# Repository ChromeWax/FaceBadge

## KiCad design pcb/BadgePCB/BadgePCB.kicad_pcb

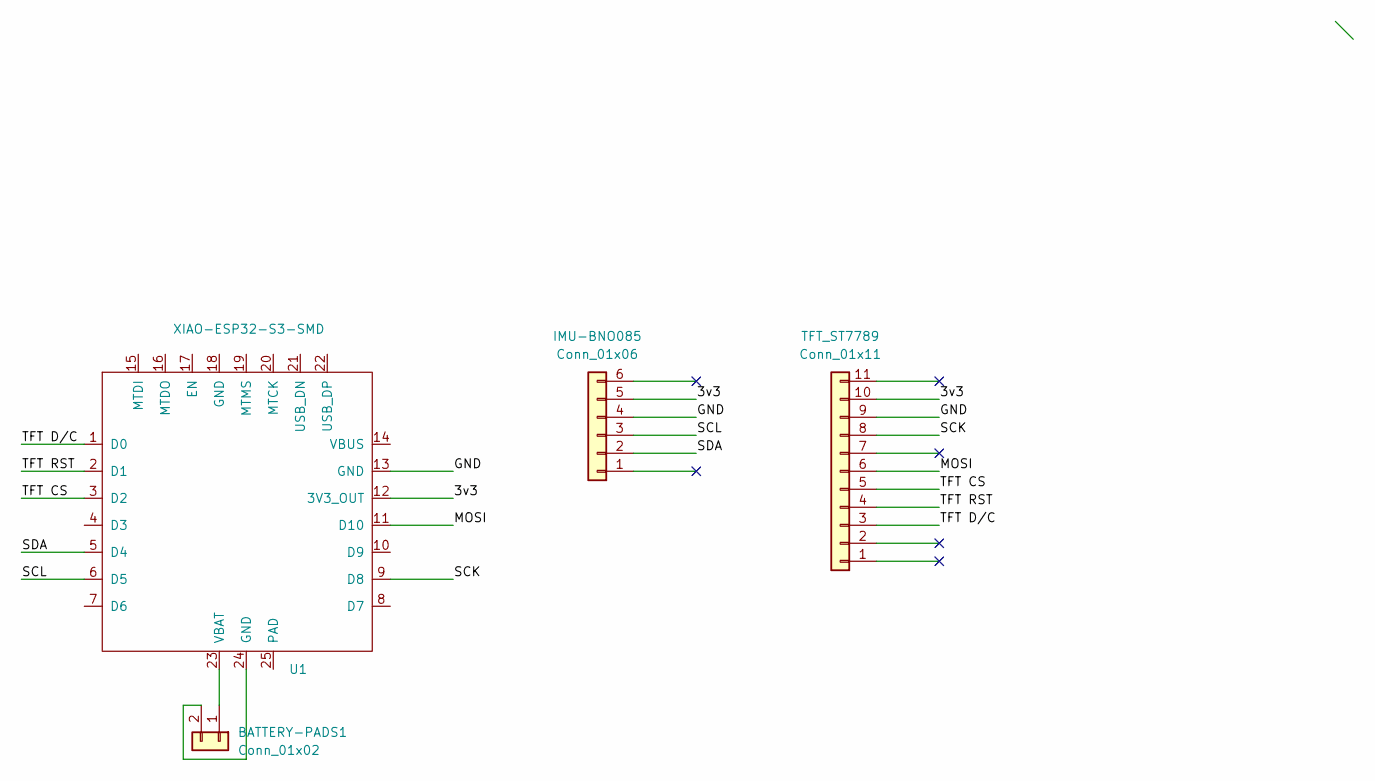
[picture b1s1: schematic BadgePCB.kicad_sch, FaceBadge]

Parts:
BATTERY-PADS1: Conn_01x02; Molex_PicoBlade_53261-0271_1x02-1MP_P1.25mm_Horizontal
IMU-BNO085: Conn_01x06; PinHeader_1x06_P2.54mm_Vertical
TFT_ST7789: Conn_01x11; PinHeader_1x11_P2.54mm_Vertical
U1: XIAO-ESP32-S3-SMD

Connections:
/3v3: IMU-BNO085.5, TFT_ST7789.10, U1.12 (3V3_OUT)
/GND: IMU-BNO085.4, TFT_ST7789.9, U1.13 (GND)
/MOSI: TFT_ST7789.6, U1.11 (D10)
/SCK: TFT_ST7789.8, U1.9 (D8)
/SCL: IMU-BNO085.3, U1.6 (D5)
/SDA: IMU-BNO085.2, U1.5 (D4)
/TFT CS: TFT_ST7789.5, U1.3 (D2)
/TFT D/C: TFT_ST7789.3, U1.1 (D0)
/TFT RST: TFT_ST7789.4, U1.2 (D1)
unnamed: BATTERY-PADS1.1, U1.23 (VBAT)
unnamed: BATTERY-PADS1.2, U1.24 (GND)

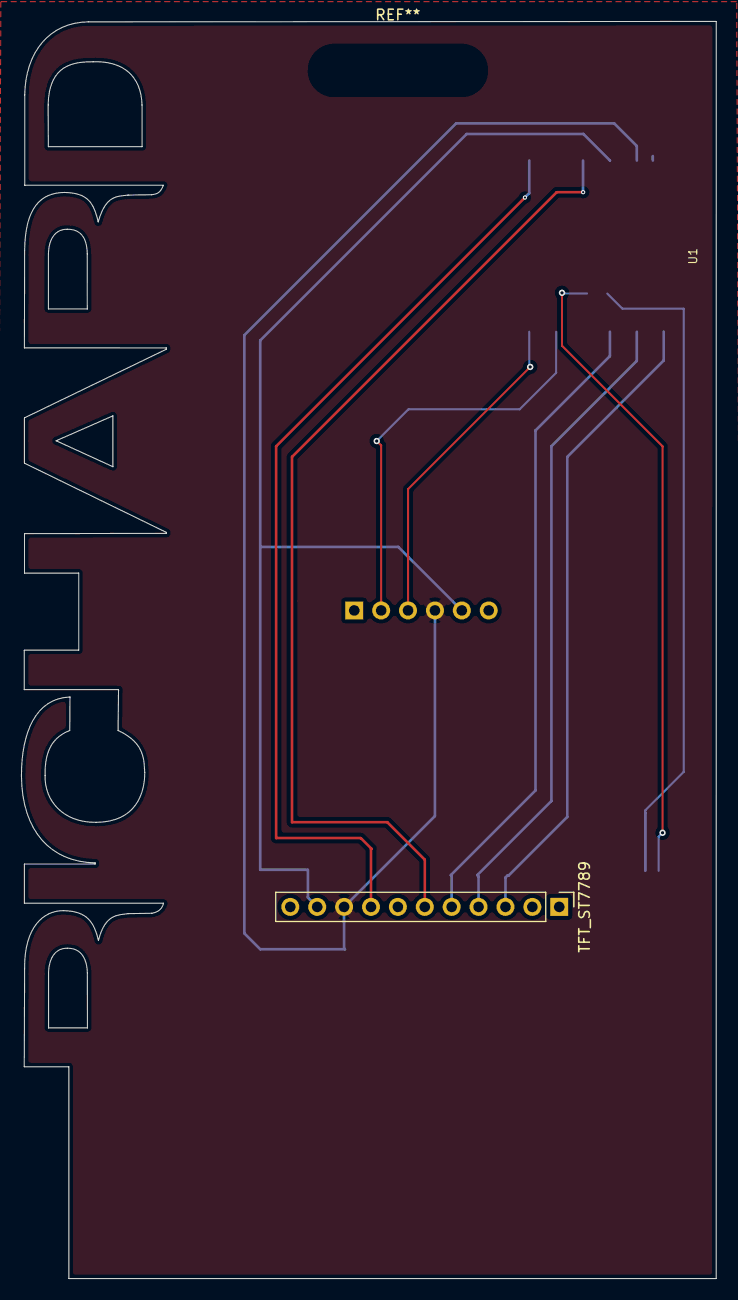
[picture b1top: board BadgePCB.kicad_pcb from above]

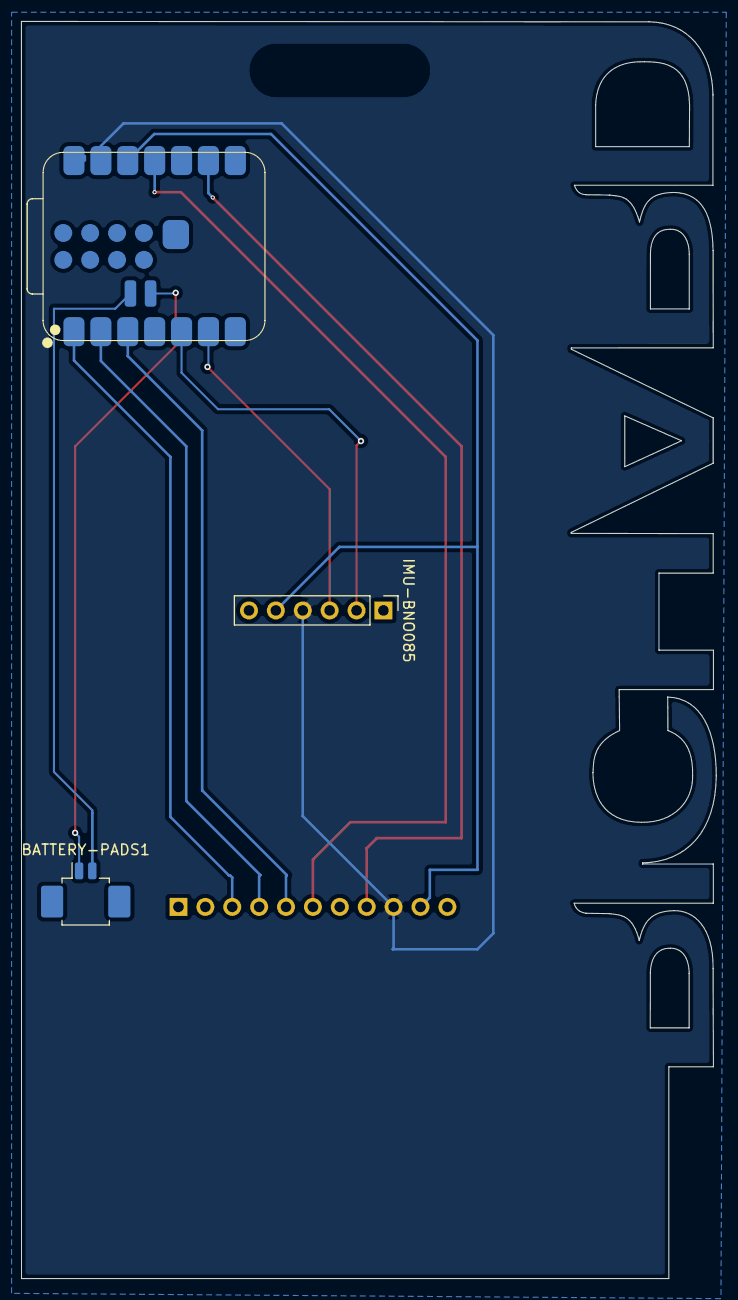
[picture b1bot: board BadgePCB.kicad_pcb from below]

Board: 2 copper layers, 65.6 x 118.7 mm, 4 parts (3 on the bottom side), 11 nets.

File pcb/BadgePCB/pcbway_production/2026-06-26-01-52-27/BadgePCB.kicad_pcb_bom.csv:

Designator,Quantity,Value,Footprint,Package,MPN,DNP,Mount_Type,Description,KiLib_Generator
BATTERY-PADS1,1,Conn_01x02,JST_GH_SM02B-GHS-TB_1x02-1MP_P1.25mm_Horizontal,,,,smt,"Generic connector, single row, 01x02, script generated (kicad-library-utils/schlib/autogen/connector/)",connector/SMD_single_row_plus_mounting_pad
IMU-BNO085,1,Conn_01x06,PinHeader_1x06_P2.54mm_Vertical,,,,tht,"Generic connector, single row, 01x06, script generated (kicad-library-utils/schlib/autogen/connector/)",connector/pin_header_socket
TFT_ST7789,1,Conn_01x11,PinHeader_1x11_P2.54mm_Vertical,,,,tht,"Generic connector, single row, 01x11, script generated (kicad-library-utils/schlib/autogen/connector/)",connector/pin_header_socket
U1,1,XIAO-ESP32-S3-SMD,XIAO-ESP32-S3-SMD,,,,tht,,

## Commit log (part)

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2026-06-22 More chnages
2026-06-23 Files
2026-06-23 Remove unused files
2026-06-23 Remove old
2026-06-23 Chnages
2026-06-23 More Changes
2026-06-23 Cleanup
2026-06-23 More cleanup
2026-06-24 Add PCB files
2026-06-24 Add Seeed Studio libraries
2026-06-24 Update PCB
2026-06-25 Designs
2026-06-25 More kicad changes
2026-06-26 Small Updates to PCB
